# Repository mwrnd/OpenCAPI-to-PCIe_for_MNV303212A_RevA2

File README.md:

**Work-In-Progress**: Notes need updating. v1.1 Gerbers need to be manufactured and tested.

# PCIe to Innova-2 MNV303212A RevA2 SlimSAS8x

This is a variant of the [OpenCAPI-to-PCIe](https://github.com/mwrnd/OpenCAPI-to-PCIe) project optimized for the **Innova-2 MNV303212A Rev:A2**.

The [Open Coherant Accelerator Processor Interface (OpenCAPI)](https://opencapi.org/wp-content/uploads/2022/07/OpenCAPI-Overview.pdf) [was a standard](https://opencapi.org/2022/08/09/cxl-consortium-and-opencapi-consortium-sign-letter-of-intent-to-transfer-opencapi-specifications-to-cxl/) that had FPGA-based [Advanced Accelerated Cable (AAC)](https://files.openpower.foundation/s/xSQPe6ypoakKQdq/download/25Gbps-spec-20171108.pdf) [Add-In cards](https://opencapi.org/wp-content/uploads/2018/12/OpenCAPI-Tech-SC18-Exhibitor-Forum.pdf) such as [ADM-PCIE-9H3](https://www.alpha-data.com/product/adm-pcie-9h3/), [ADM-PCIE-9H7](https://www.alpha-data.com/alpha-data-release-adm-pcie-9h7-data-center-board-with-xilinx-virtex-ultrascale-hbm-fpga/), [ADM-PCIE-9V3](https://www.alpha-data.com/product/adm-pcie-9v3/), [ADM-PCIE-9V5](https://www.alpha-data.com/product/adm-pcie-9v5/), [BittWare XUP-VV4](https://www.bittware.com/fpga/xup-vv4/), [BittWare XUP-VVH](https://www.bittware.com/fpga/xup-vvh/), and [Nvidia Innova-2 Flex SmartNIC](https://www.nvidia.com/en-us/networking/ethernet/innova-2-flex/).

The OpenCAPI interface is based on [PCI-Express](https://en.wikipedia.org/wiki/PCI_Express) and uses a [SlimSAS 8X](https://en.wikipedia.org/wiki/Serial_Attached_SCSI) (SFF-8654) Connector. This adapter enables connecting an OpenCAPI FPGA board to a host using PCIe over a SlimSAS cable.

## PCB Layout

4-Layer PCB. Inner 2 layers are GND planes. Differential pair are matched to a length of 61mm +/- 1mm both inter-pair and intra-pair (N-to-P).

## Schematic

Note the reverse channel ordering and swapped `_P` and `_N` for RX3, 4, and 7. This is done to optimize for the `MNV303212A-ADLT Rev:A2` board. Technically it should not matter. PCIe features automatic `_P-to-_N` swapping and the FPGA supports arbitrary lane assignment. I did this to eliminate all possible conflating problems while tracking down reliability issues.

## Design Notes

Only a single component is needed for the adapter, a [U10A474200T](https://www.digikey.com/en/products/detail/amphenol-cs-commercial-products/U10A474200T/14632855)/[U10A474240T](https://www.digikey.com/en/products/detail/amphenol-cs-commercial-products/U10A474240T/17066204) SlimSAS 8x Right-Angle SMD Connector.

A SlimSAS 8x Cable such as the [3M 8ES8-1DF21](https://www.trustedparts.com/en/search/8ES8-1DF21)([Datasheet](https://multimedia.3m.com/mws/media/1398233O/3m-slimline-twin-ax-assembly-sff-8654-x8-30awg-78-5100-2665-8.pdf)) is required to use the adapter with an OpenCAPI FPGA Board.

Resistor **R1** is shorted to connect `nPRSNT1` to `nPRSNT2_x8`. The trace can be scratched off and `nPRSNT1` can be connected to `nPRSNT2_x1` or `nPRSNT2_x4` to limit the PCIe lane width.

### PCB Stackup

I am using values from [JLCPCB](https://jlcpcb.com/capabilities/pcb-capabilities).

### Trace Impedance Control

OpenCAPI uses 85ohm impedance cables. I played with the values until I got the loosest differential pair coupling that is manufacturable with larger tolerances.

## Testing

The [innova2_xdma_opencapi](https://github.com/mwrnd/innova2_xdma_opencapi) project is designed to test this `OpenCAPI-to-PCIe for MNV303212A RevA2` Adapter using an [Innova2 Flex SmartNIC Rev:A2 board](https://github.com/mwrnd/innova2_flex_xcku15p_notes).

The Innova2 SmartNIC's XCKU15P FPGA does not have its Configuration Block in the same column as the OpenCAPI GTY transceivers so it is impossible to configure the FPGA within the [PCIe Specification's 100ms time limit](https://pcisig.com/specifications/ecr_ecn_process?speclib=100+ms).

Motherboard boot must therefore be delayed to allow the FPGA to configure itself before the OpenCAPI-to-PCIe device is enumerated by the host system. This can be accomplished by toggling the POWER button, then pressing and holding the RESET button for a second before releasing it. Or, [connect a capacitor across the reset pins of an ATX motherboard's Front Panel Header](https://github.com/mwrnd/ATX_Boot_Delay):

### Cable Performance

Using a [3M 8ES8-1DF21-0.75](https://www.trustedparts.com/en/search/8ES8-1DF21-0.75) cable:

PCIe Link Status is usually excellent:

Using an [SFPCables.com SFF-8654 to SFF-8654 8i](https://www.sfpcables.com/24g-internal-slimsas-sff-8654-to-sff-8654-8i-cable-straight-to-90-degree-left-angle-8x-12-sas-4-0-85-ohm-0-5-1-meter) cable:

PCIe Link Status is downgraded:

### Additional OpenCAPI Signals

Additional useful signals from the OpenCAPI connector are routed to a 6x1 0.1" Header ([DigiKey](https://www.digikey.com/en/products/detail/sullins-connector-solutions/PPTC061LFBN-RC/810145)). The pinout matches a [TC74 I2C Temperature Sensor](https://www.microchip.com/en-us/product/tc74) ([DigiKey](https://www.digikey.com/en/products/detail/microchip-technology/TC74A0-3-3VAT/442720)) for testing I2C. I2C pull-ups are on the AAC Add-in card (Innova-2). Note 3.3V is from the PCIe connector. **PRE** is a Presence Detect pin which is connected to GND via a 50-Ohm resistor on the OpenCAPI AAC Add-In card (Innova-2). **RST** is connected to PCIe/OpenCAPI RESET.

The [innova2_xdma_opencapi](https://github.com/mwrnd/innova2_xdma_opencapi) project features the ability to [test](https://github.com/mwrnd/innova2_xdma_opencapi/blob/main/README.md#opencapi-i2c-over-xdma) a TC74Ax-3.3VAT in an OpenCAPI-to-PCIe Adapter.

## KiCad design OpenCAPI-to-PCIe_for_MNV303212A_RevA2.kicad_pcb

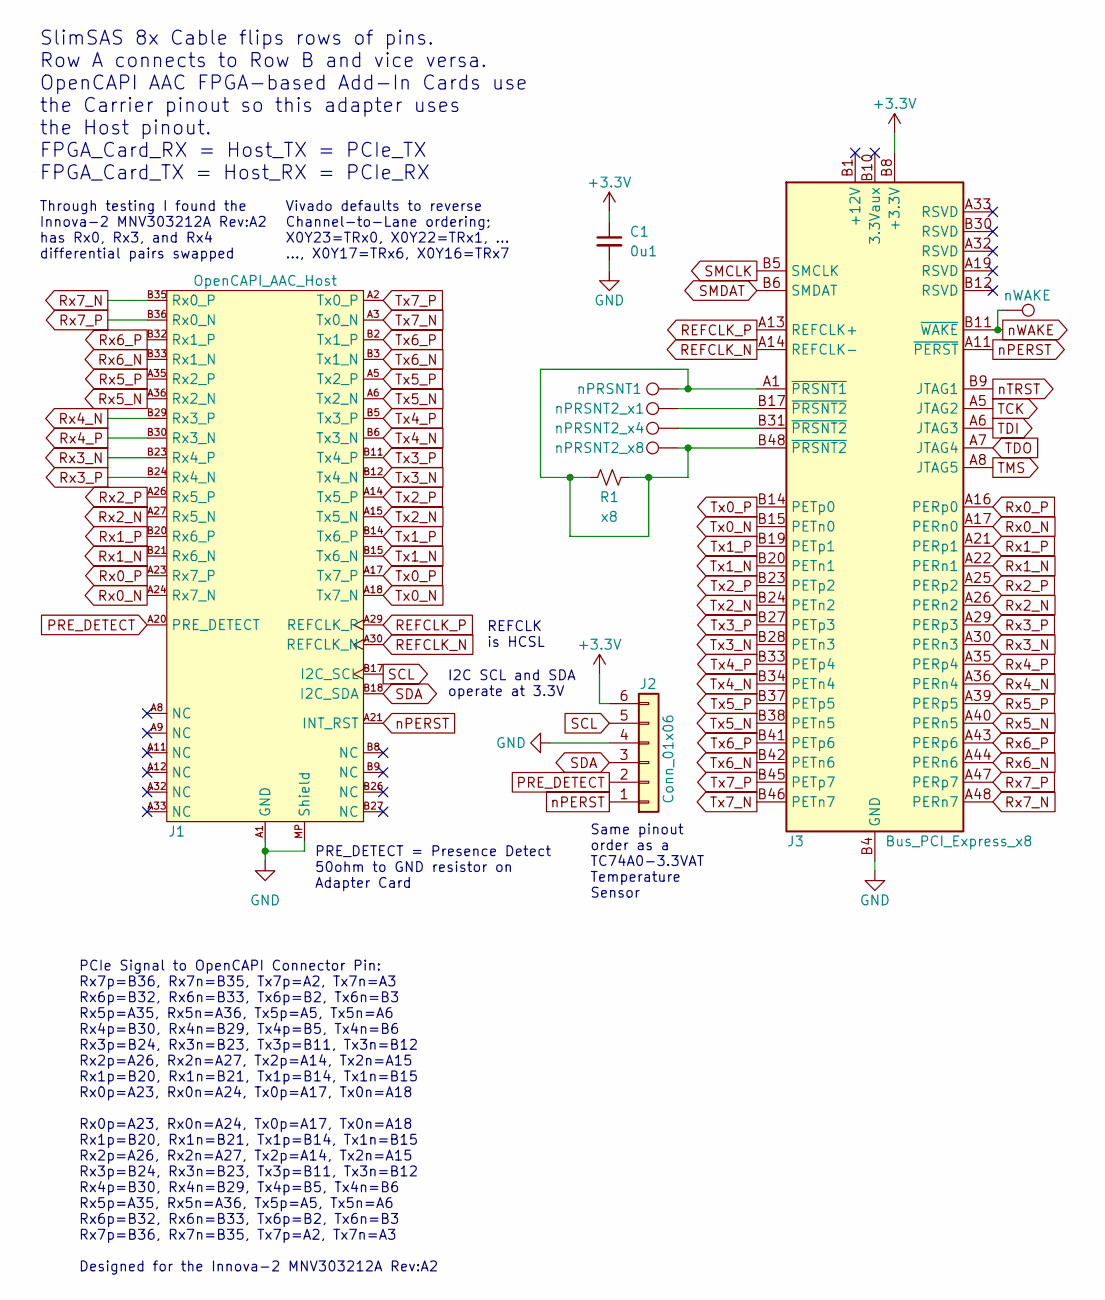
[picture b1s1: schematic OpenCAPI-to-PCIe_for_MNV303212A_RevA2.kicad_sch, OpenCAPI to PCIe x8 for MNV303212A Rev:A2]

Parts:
C1: 0u1; C_0805_2012Metric_Pad1.18x1.45mm_HandSolder
J1: OpenCAPI_AAC_Host; SlimSAS_8x_RA_U10-A474
J2: Conn_01x06; PinHeader_1x06_P2.54mm_Vertical
J3: Bus_PCI_Express_x8; BUS_PCIexpress_x8
R1: x8; R_0603_1608Metric_Pad0.98x0.95mm_HandSolder
TP1: nPRSNT1; TestPoint_THTPad_D1.0mm_Drill0.5mm
TP2: nPRSNT2_x1; TestPoint_THTPad_D1.0mm_Drill0.5mm
TP3: nPRSNT2_x4; TestPoint_THTPad_D1.0mm_Drill0.5mm
TP4: nWAKE; TestPoint_THTPad_D1.0mm_Drill0.5mm
TP5: nPRSNT2_x8; TestPoint_THTPad_D1.0mm_Drill0.5mm

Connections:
+3.3V: C1.1, J2.6, J3.A9 (+3.3V), J3.A10 (+3.3V), J3.B8 (+3.3V)
GND: C1.2, J1.A1 (GND), J1.A4 (GND), J1.A7 (GND), J1.A10 (GND), J1.A13 (GND), J1.A16 (GND), J1.A19 (GND), J1.A22 (GND), J1.A25 (GND), J1.A28 (GND), J1.A31 (GND), J1.A34 (GND), J1.A37 (GND), J1.B1 (GND), J1.B4 (GND), J1.B7 (GND), J1.B10 (GND), J1.B13 (GND), J1.B16 (GND), J1.B19 (GND), J1.B22 (GND), J1.B25 (GND), J1.B28 (GND), J1.B31 (GND), J1.B34 (GND), J1.B37 (GND), J1.MP (Shield), J2.4, J3.A4 (GND), J3.A12 (GND), J3.A15 (GND), J3.A18 (GND), J3.A20 (GND), J3.A23 (GND), J3.A24 (GND), J3.A27 (GND), J3.A28 (GND), J3.A31 (GND), J3.A34 (GND), J3.A37 (GND), J3.A38 (GND), J3.A41 (GND), J3.A42 (GND), J3.A45 (GND), J3.A46 (GND), J3.A49 (GND), J3.B4 (GND), J3.B7 (GND), J3.B13 (GND), J3.B16 (GND), J3.B18 (GND), J3.B21 (GND), J3.B22 (GND), J3.B25 (GND), J3.B26 (GND), J3.B29 (GND), J3.B32 (GND), J3.B35 (GND), J3.B36 (GND), J3.B39 (GND), J3.B40 (GND), J3.B43 (GND), J3.B44 (GND), J3.B47 (GND), J3.B49 (GND)
unnamed: J3.A1 (~PRSNT1), J3.B48 (~PRSNT2), R1.1, R1.2, TP1.1, TP5.1
unnamed: J3.B17 (~PRSNT2), TP2.1
unnamed: J3.B31 (~PRSNT2), TP3.1
PRE_DETECT: J1.A20 (PRE_DETECT), J2.2
REFCLK_N: J1.A30 (REFCLK_N), J3.A14 (REFCLK-)
REFCLK_P: J1.A29 (REFCLK_P), J3.A13 (REFCLK+)
Rx0_N: J1.A24 (Rx7_N), J3.A17 (PERn0)
Rx0_P: J1.A23 (Rx7_P), J3.A16 (PERp0)
Rx1_N: J1.B21 (Rx6_N), J3.A22 (PERn1)
Rx1_P: J1.B20 (Rx6_P), J3.A21 (PERp1)
Rx2_N: J1.A27 (Rx5_N), J3.A26 (PERn2)
Rx2_P: J1.A26 (Rx5_P), J3.A25 (PERp2)
Rx3_N: J1.B23 (Rx4_P), J3.A30 (PERn3)
Rx3_P: J1.B24 (Rx4_N), J3.A29 (PERp3)
Rx4_N: J1.B29 (Rx3_P), J3.A36 (PERn4)
Rx4_P: J1.B30 (Rx3_N), J3.A35 (PERp4)
Rx5_N: J1.A36 (Rx2_N), J3.A40 (PERn5)
Rx5_P: J1.A35 (Rx2_P), J3.A39 (PERp5)
Rx6_N: J1.B33 (Rx1_N), J3.A44 (PERn6)
Rx6_P: J1.B32 (Rx1_P), J3.A43 (PERp6)
Rx7_N: J1.B35 (Rx0_P), J3.A48 (PERn7)
Rx7_P: J1.B36 (Rx0_N), J3.A47 (PERp7)
SCL: J1.B17 (I2C_SCL), J2.5
SDA: J1.B18 (I2C_SDA), J2.3
SMCLK: J3.B5 (SMCLK)
SMDAT: J3.B6 (SMDAT)
TCK: J3.A5 (JTAG2)
TDI: J3.A6 (JTAG3)
TDO: J3.A7 (JTAG4)
TMS: J3.A8 (JTAG5)
Tx0_N: J1.A18 (Tx7_N), J3.B15 (PETn0)
Tx0_P: J1.A17 (Tx7_P), J3.B14 (PETp0)
Tx1_N: J1.B15 (Tx6_N), J3.B20 (PETn1)
Tx1_P: J1.B14 (Tx6_P), J3.B19 (PETp1)
Tx2_N: J1.A15 (Tx5_N), J3.B24 (PETn2)
Tx2_P: J1.A14 (Tx5_P), J3.B23 (PETp2)
Tx3_N: J1.B12 (Tx4_N), J3.B28 (PETn3)
Tx3_P: J1.B11 (Tx4_P), J3.B27 (PETp3)
Tx4_N: J1.B6 (Tx3_N), J3.B34 (PETn4)
Tx4_P: J1.B5 (Tx3_P), J3.B33 (PETp4)
Tx5_N: J1.A6 (Tx2_N), J3.B38 (PETn5)
Tx5_P: J1.A5 (Tx2_P), J3.B37 (PETp5)
Tx6_N: J1.B3 (Tx1_N), J3.B42 (PETn6)
Tx6_P: J1.B2 (Tx1_P), J3.B41 (PETp6)
Tx7_N: J1.A3 (Tx0_N), J3.B46 (PETn7)
Tx7_P: J1.A2 (Tx0_P), J3.B45 (PETp7)
nPERST: J1.A21 (INT_RST), J2.1, J3.A11 (~PERST)
nTRST: J3.B9 (JTAG1)
nWAKE: J3.B11 (~WAKE), TP4.1

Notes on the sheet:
I2C SCL and SDA operate at 3.3V
Same pinout order as a TC74A0-3.3VAT Temperature Sensor
Vivado defaults to reverse Channel-to-Lane ordering; X0Y23=TRx0, X0Y22=TRx1, ... ..., X0Y17=TRx6, X0Y16=TRx7
REFCLK is HCSL
PCIe Signal to OpenCAPI Connector Pin: Rx7p=B36, Rx7n=B35, Tx7p=A2, Tx7n=A3 Rx6p=B32, Rx6n=B33, Tx6p=B2, Tx6n=B3 Rx5p=A35, Rx5n=A36, Tx5p=A5, Tx5n=A6 Rx4p=B30, Rx4n=B29, Tx4p=B5, Tx4n=B6 Rx3p=B24, Rx3n=B23, Tx3p=B11, Tx3n=B12 Rx2p=A26, Rx2n=A27, Tx2p=A14, Tx2n=A15 Rx1p=B20, Rx1n=B21, Tx1p=B14, Tx1n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
SlimSAS 8x Cable flips rows of pins. Row A connects to Row B and vice versa. OpenCAPI AAC FPGA-based Add-In Cards use the Carrier pinout so this adapter uses the Host pinout. FPGA_Card_RX = Host_TX = PCIe_TX FPGA_Card_TX = Host_RX = PCIe_RX
PRE_DETECT = Presence Detect 50ohm to GND resistor on Adapter Card
Through testing I found the Innova-2 MNV303212A Rev:A2 has Rx0, Rx3, and Rx4 differential pairs swapped

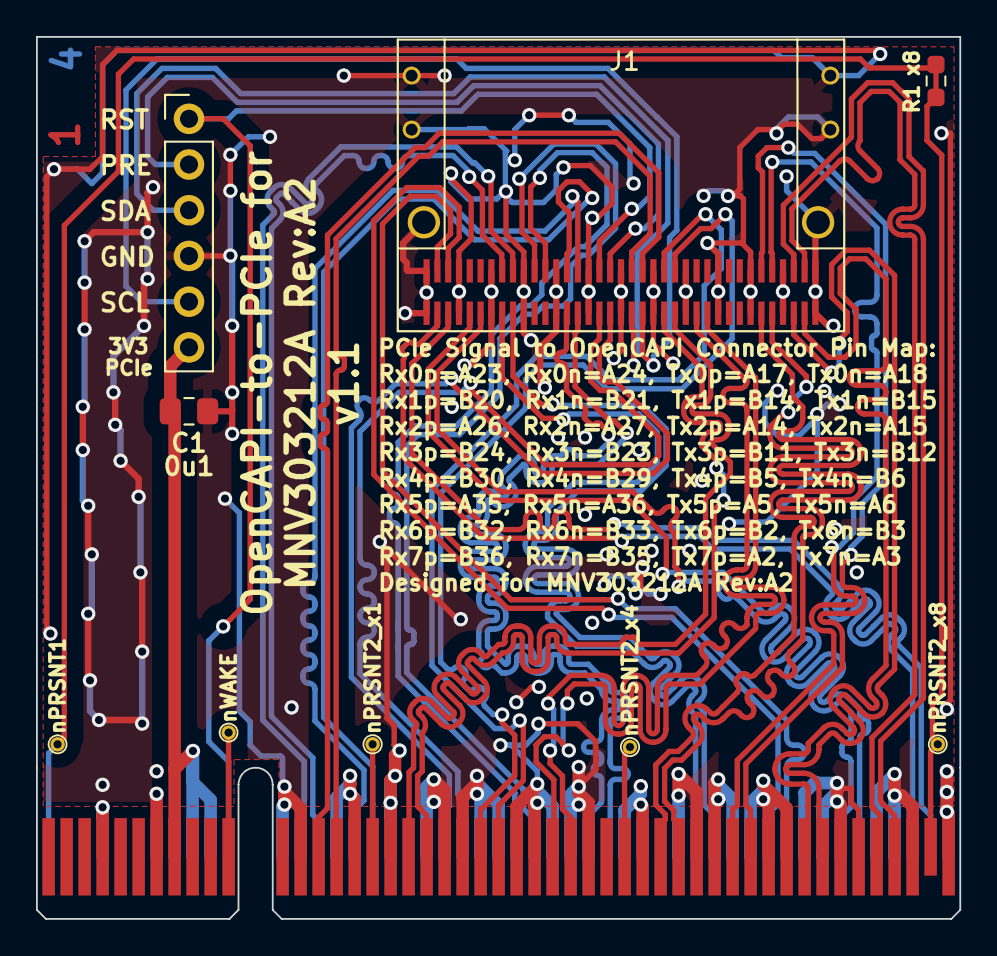
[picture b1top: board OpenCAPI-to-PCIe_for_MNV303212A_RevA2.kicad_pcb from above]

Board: 4 copper layers, 51.3 x 49.0 mm, 10 parts (0 on the bottom side), 44 nets.
